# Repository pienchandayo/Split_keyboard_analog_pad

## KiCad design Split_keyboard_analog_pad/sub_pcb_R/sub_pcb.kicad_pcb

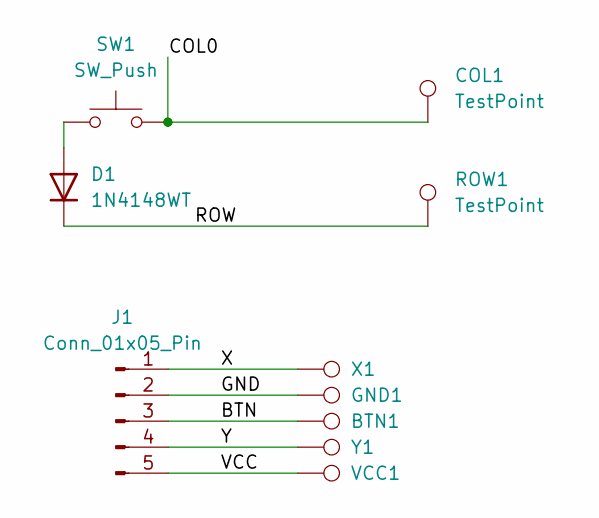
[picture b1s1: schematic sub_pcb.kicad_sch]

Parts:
BTN1: TestPoint; TestPoint_Pad_1.5x1.5mm
COL1: TestPoint; TestPoint_Pad_1.5x1.5mm
D1: 1N4148WT; D_SOD-523
GND1: TestPoint; TestPoint_Pad_1.5x1.5mm
J1: Conn_01x05_Pin; Switch_joy_pad
ROW1: TestPoint; TestPoint_Pad_1.5x1.5mm
SW1: SW_Push; SW_Kailh_Choc_V1V2_1.00u
VCC1: TestPoint; TestPoint_Pad_1.5x1.5mm
X1: TestPoint; TestPoint_Pad_1.5x1.5mm
Y1: TestPoint; TestPoint_Pad_1.5x1.5mm

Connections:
/BTN: BTN1.1, J1.3
/COL0: COL1.1, SW1.2
/GND: GND1.1, J1.2
/ROW: D1.1 (K), ROW1.1
/VCC: J1.5, VCC1.1
/X: J1.1, X1.1
/Y: J1.4, Y1.1
unnamed: D1.2 (A), SW1.1

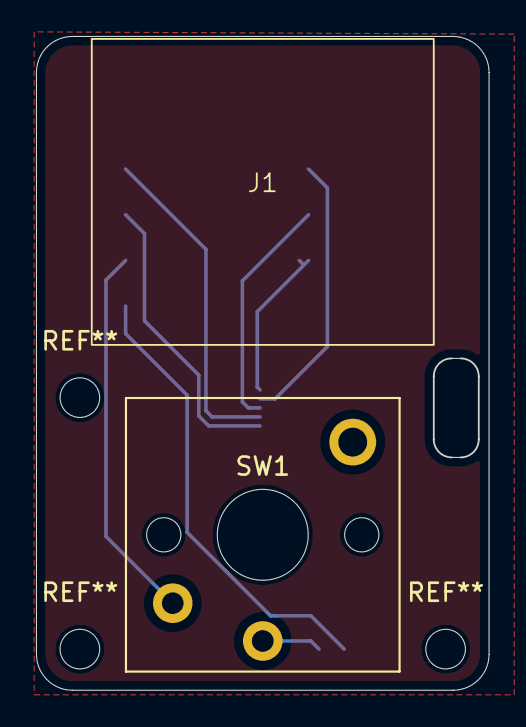
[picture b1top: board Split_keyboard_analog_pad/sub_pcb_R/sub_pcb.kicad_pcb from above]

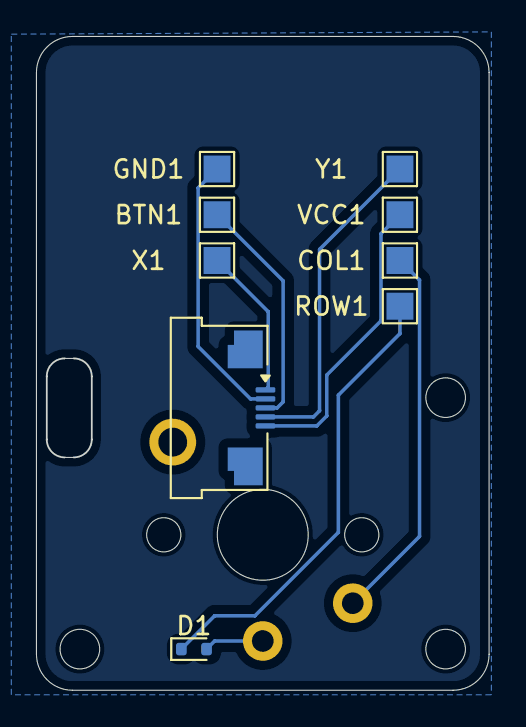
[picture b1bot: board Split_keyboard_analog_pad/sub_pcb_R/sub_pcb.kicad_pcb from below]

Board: 2 copper layers, 25.1 x 36.3 mm, 10 parts (8 on the bottom side), 8 nets.

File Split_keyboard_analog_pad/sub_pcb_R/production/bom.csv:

Designator,Footprint,Quantity,Value,LCSC Part #
"BTN1, COL1, GND1, ROW1, VCC1, X1, Y1",TestPoint_Pad_1.5x1.5mm,7,TestPoint,
D1,D_SOD-523,1,1N4148WT,
J1,Switch_joy_pad,1,Conn_01x05_Pin,
SW1,SW_Kailh_Choc_V1V2_1.00u,1,SW_Push,

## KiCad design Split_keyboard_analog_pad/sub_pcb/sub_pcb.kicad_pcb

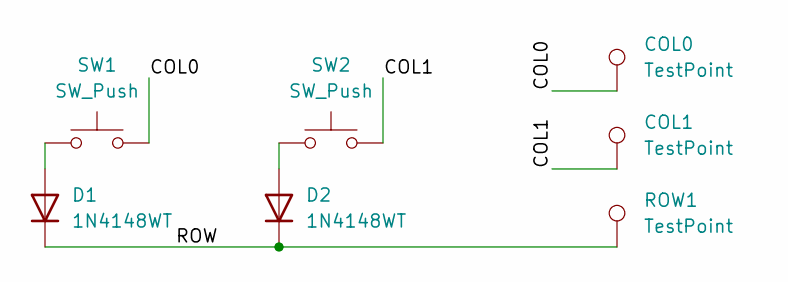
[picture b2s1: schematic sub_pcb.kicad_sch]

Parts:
COL0, COL1: TestPoint; TestPoint_Pad_1.5x1.5mm
D1, D2: 1N4148WT; D_SOD-523
ROW1: TestPoint; TestPoint_Pad_1.5x1.5mm
SW1, SW2: SW_Push; SW_Kailh_Choc_V1V2_1.00u

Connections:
/COL0: COL0.1, SW1.2
/COL1: COL1.1, SW2.2
/ROW: D1.1 (K), D2.1 (K), ROW1.1
unnamed: D1.2 (A), SW1.1
unnamed: D2.2 (A), SW2.1

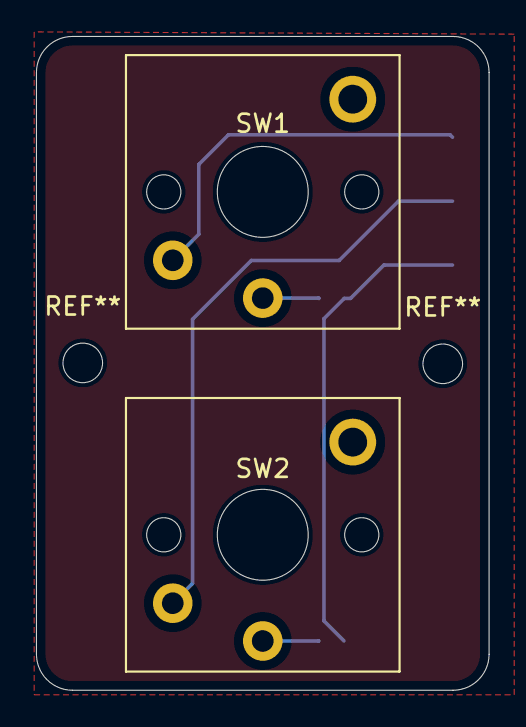
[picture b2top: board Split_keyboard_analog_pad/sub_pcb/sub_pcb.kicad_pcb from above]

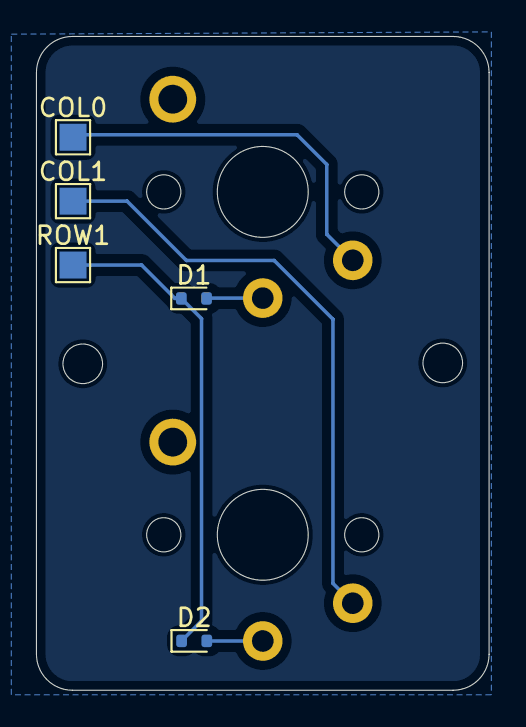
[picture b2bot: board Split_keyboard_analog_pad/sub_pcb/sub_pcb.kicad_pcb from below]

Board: 2 copper layers, 25.1 x 36.3 mm, 7 parts (5 on the bottom side), 5 nets.

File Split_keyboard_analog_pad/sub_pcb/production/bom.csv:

Designator,Footprint,Quantity,Value,LCSC Part #
"COL0, COL1, ROW1",TestPoint_Pad_1.5x1.5mm,3,TestPoint,
"D1, D2",D_SOD-523,2,1N4148WT,
"SW1, SW2",SW_Kailh_Choc_V1V2_1.00u,2,SW_Push,

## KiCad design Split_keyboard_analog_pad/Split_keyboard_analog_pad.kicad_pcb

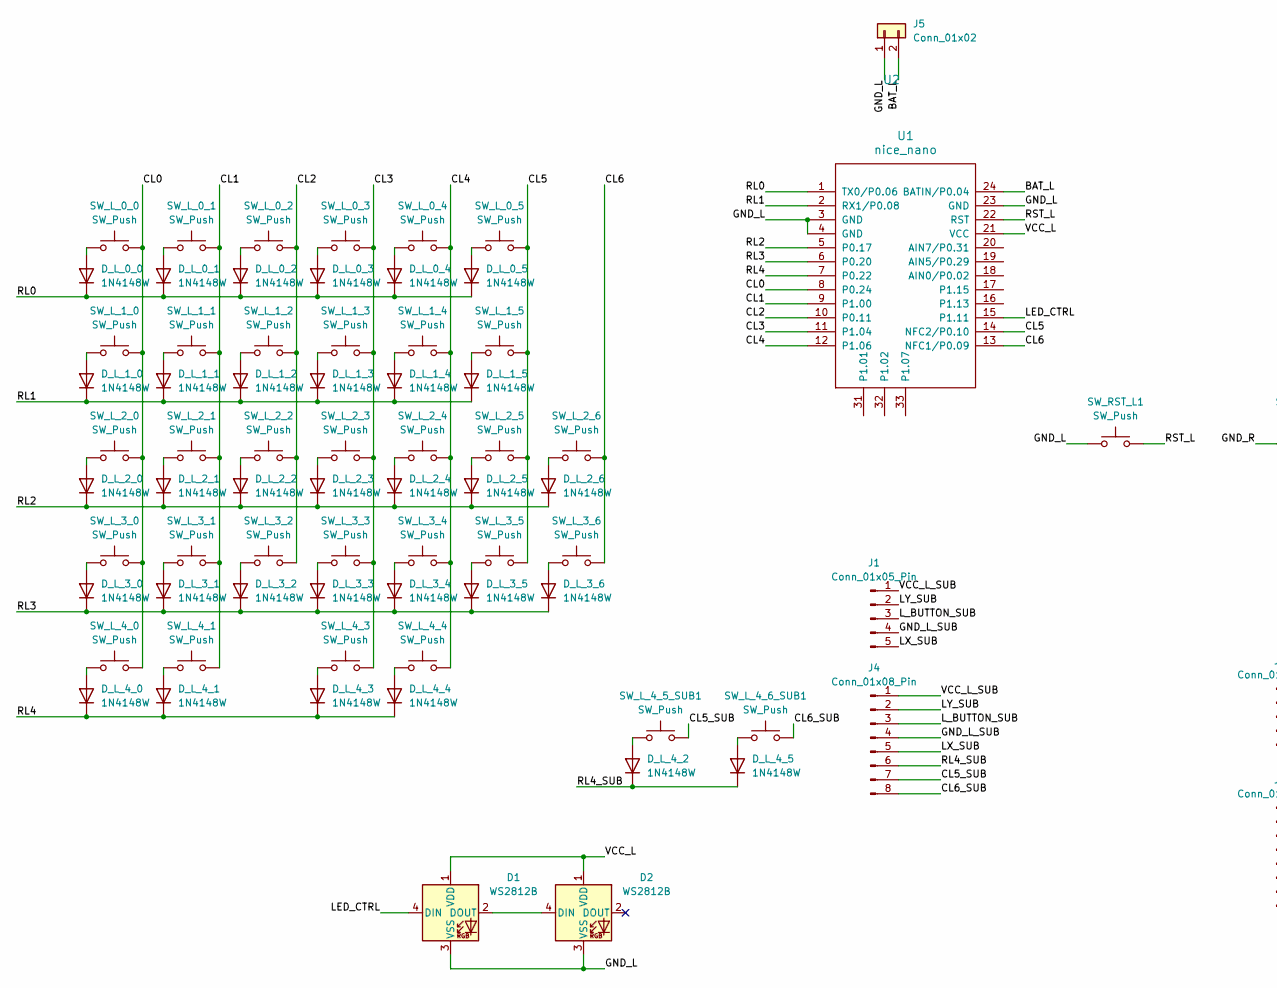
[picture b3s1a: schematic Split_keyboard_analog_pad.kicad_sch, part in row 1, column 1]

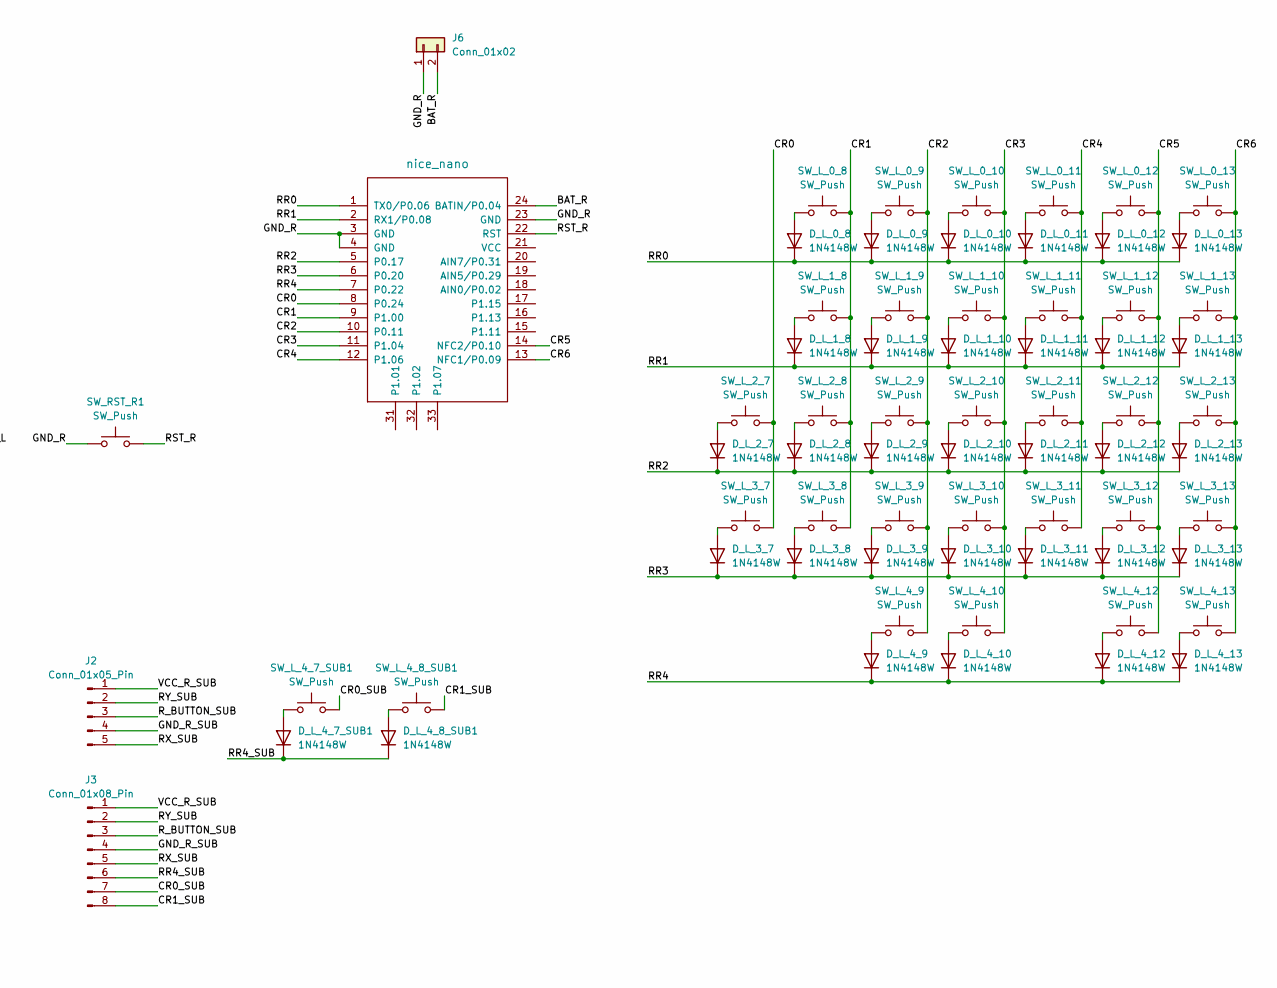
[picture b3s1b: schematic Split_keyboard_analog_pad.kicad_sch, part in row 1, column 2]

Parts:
D1, D2: WS2812B; LED_WS2812B_PLCC4_5.0x5.0mm_P3.2mm
D_L_0_0, D_L_0_1, D_L_0_2, D_L_0_3, D_L_0_4, D_L_0_5, D_L_0_8, D_L_0_9, D_L_0_10, D_L_0_11, D_L_0_12, D_L_0_13, D_L_1_0, D_L_1_1, D_L_1_2, D_L_1_3, D_L_1_4, D_L_1_5, D_L_1_8, D_L_1_9, D_L_1_10, D_L_1_11, D_L_1_12, D_L_1_13, D_L_2_0, D_L_2_1, D_L_2_2, D_L_2_3, D_L_2_4, D_L_2_5, D_L_2_6, D_L_2_7, D_L_2_8, D_L_2_9, D_L_2_10, D_L_2_11, D_L_2_12, D_L_2_13, D_L_3_0, D_L_3_1, D_L_3_2, D_L_3_3, D_L_3_4, D_L_3_5, D_L_3_6, D_L_3_7, D_L_3_8, D_L_3_9, D_L_3_10, D_L_3_11, D_L_3_12, D_L_3_13, D_L_4_0, D_L_4_1, D_L_4_2, D_L_4_3, D_L_4_4, D_L_4_5, D_L_4_7_SUB1, D_L_4_8_SUB1, D_L_4_9, D_L_4_10, D_L_4_12, D_L_4_13: 1N4148W; D_SOD-123
J1, J2: Conn_01x05_Pin; Switch_joy_pad
J3, J4: Conn_01x08_Pin; PinHeader_1x08_P2.54mm_Vertical
J5, J6: Conn_01x02; JST_PH_S2B-PH-SM4-TB_1x02-1MP_P2.00mm_Horizontal
SW_L_0_0, SW_L_0_1, SW_L_0_2, SW_L_0_3, SW_L_0_4, SW_L_0_5, SW_L_0_8, SW_L_0_9, SW_L_0_10, SW_L_0_11, SW_L_0_12, SW_L_0_13, SW_L_1_0, SW_L_1_1, SW_L_1_2, SW_L_1_3, SW_L_1_4, SW_L_1_5, SW_L_1_8, SW_L_1_9, SW_L_1_10, SW_L_1_11, SW_L_1_12, SW_L_1_13, SW_L_2_0, SW_L_2_1, SW_L_2_2, SW_L_2_3, SW_L_2_4, SW_L_2_5, SW_L_2_6, SW_L_2_7, SW_L_2_8, SW_L_2_9, SW_L_2_10, SW_L_2_11, SW_L_2_12, SW_L_2_13, SW_L_3_0, SW_L_3_1, SW_L_3_2, SW_L_3_3, SW_L_3_4, SW_L_3_5, SW_L_3_6, SW_L_3_7, SW_L_3_8, SW_L_3_9, SW_L_3_10, SW_L_3_11, SW_L_3_12, SW_L_3_13, SW_L_4_0, SW_L_4_1, SW_L_4_3, SW_L_4_10, SW_L_4_12, SW_L_4_13: SW_Push; SW_Hotswap_Kailh_MX_1.00u
SW_L_4_4, SW_L_4_9: SW_Push; SW_Hotswap_Kailh_MX_2.00u
SW_L_4_5_SUB1, SW_L_4_6_SUB1, SW_L_4_7_SUB1, SW_L_4_8_SUB1: SW_Push; SW_Kailh_Choc_V2_1.00u
SW_RST_L1: SW_Push; SW_SPST_Omron_B3FS-100xP
SW_RST_R1: SW_Push; SW_SPST_Omron_B3FS-100xP
U1, U2: nice_nano

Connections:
/BAT_L: J5.2, U1.24 (BATIN/P0.04)
/BAT_R: J6.2, U2.24 (BATIN/P0.04)
/CL0: SW_L_0_0.2, SW_L_1_0.2, SW_L_2_0.2, SW_L_3_0.2, SW_L_4_0.2, U1.8 (P0.24)
/CL1: SW_L_0_1.2, SW_L_1_1.2, SW_L_2_1.2, SW_L_3_1.2, SW_L_4_1.2, U1.9 (P1.00)
/CL2: SW_L_0_2.2, SW_L_1_2.2, SW_L_2_2.2, SW_L_3_2.2, U1.10 (P0.11)
/CL3: SW_L_0_3.2, SW_L_1_3.2, SW_L_2_3.2, SW_L_3_3.2, SW_L_4_3.2, U1.11 (P1.04)
/CL4: SW_L_0_4.2, SW_L_1_4.2, SW_L_2_4.2, SW_L_3_4.2, SW_L_4_4.2, U1.12 (P1.06)
/CL5: SW_L_0_5.2, SW_L_1_5.2, SW_L_2_5.2, SW_L_3_5.2, U1.14 (NFC2/P0.10)
/CL5_SUB: J4.7, SW_L_4_5_SUB1.2
/CL6: SW_L_2_6.2, SW_L_3_6.2, U1.13 (NFC1/P0.09)
/CL6_SUB: J4.8, SW_L_4_6_SUB1.2
/CR0: SW_L_2_7.2, SW_L_3_7.2, U2.8 (P0.24)
/CR0_SUB: J3.7, SW_L_4_7_SUB1.2
/CR1: SW_L_0_8.2, SW_L_1_8.2, SW_L_2_8.2, SW_L_3_8.2, U2.9 (P1.00)
/CR1_SUB: J3.8, SW_L_4_8_SUB1.2
/CR2: SW_L_0_9.2, SW_L_1_9.2, SW_L_2_9.2, SW_L_3_9.2, SW_L_4_9.2, U2.10 (P0.11)
/CR3: SW_L_0_10.2, SW_L_1_10.2, SW_L_2_10.2, SW_L_3_10.2, SW_L_4_10.2, U2.11 (P1.04)
/CR4: SW_L_0_11.2, SW_L_1_11.2, SW_L_2_11.2, SW_L_3_11.2, U2.12 (P1.06)
/CR5: SW_L_0_12.2, SW_L_1_12.2, SW_L_2_12.2, SW_L_3_12.2, SW_L_4_12.2, U2.14 (NFC2/P0.10)
/CR6: SW_L_0_13.2, SW_L_1_13.2, SW_L_2_13.2, SW_L_3_13.2, SW_L_4_13.2, U2.13 (NFC1/P0.09)
/GND_L: D1.3 (VSS), D2.3 (VSS), J5.1, SW_RST_L1.1, U1.3 (GND), U1.4 (GND), U1.23 (GND)
/GND_L_SUB: J1.4, J4.4
/GND_R: J6.1, SW_RST_R1.1, U2.3 (GND), U2.4 (GND), U2.23 (GND); also elsewhere on the board
/GND_R_SUB: J2.4, J3.4
/LED_CTRL_L: D1.4 (DIN), U1.15 (P1.11)
/LED_CTRL_R: U2.15 (P1.11); also elsewhere on the board
/LX_SUB: J1.5, J4.5
/LY_SUB: J1.2, J4.2
/L_BUTTON_SUB: J1.3, J4.3
/RL0: D_L_0_0.1 (K), D_L_0_1.1 (K), D_L_0_2.1 (K), D_L_0_3.1 (K), D_L_0_4.1 (K), D_L_0_5.1 (K), U1.1 (TX0/P0.06)
/RL1: D_L_1_0.1 (K), D_L_1_1.1 (K), D_L_1_2.1 (K), D_L_1_3.1 (K), D_L_1_4.1 (K), D_L_1_5.1 (K), U1.2 (RX1/P0.08)
/RL2: D_L_2_0.1 (K), D_L_2_1.1 (K), D_L_2_2.1 (K), D_L_2_3.1 (K), D_L_2_4.1 (K), D_L_2_5.1 (K), D_L_2_6.1 (K), U1.5 (P0.17)
/RL3: D_L_3_0.1 (K), D_L_3_1.1 (K), D_L_3_2.1 (K), D_L_3_3.1 (K), D_L_3_4.1 (K), D_L_3_5.1 (K), D_L_3_6.1 (K), U1.6 (P0.20)
/RL4: D_L_4_0.1 (K), D_L_4_1.1 (K), D_L_4_3.1 (K), D_L_4_4.1 (K), U1.7 (P0.22)
/RL4_SUB: D_L_4_2.1 (K), D_L_4_5.1 (K), J4.6
/RR0: D_L_0_8.1 (K), D_L_0_9.1 (K), D_L_0_10.1 (K), D_L_0_11.1 (K), D_L_0_12.1 (K), D_L_0_13.1 (K), U2.1 (TX0/P0.06)
/RR1: D_L_1_8.1 (K), D_L_1_9.1 (K), D_L_1_10.1 (K), D_L_1_11.1 (K), D_L_1_12.1 (K), D_L_1_13.1 (K), U2.2 (RX1/P0.08)
/RR2: D_L_2_7.1 (K), D_L_2_8.1 (K), D_L_2_9.1 (K), D_L_2_10.1 (K), D_L_2_11.1 (K), D_L_2_12.1 (K), D_L_2_13.1 (K), U2.5 (P0.17)
/RR3: D_L_3_7.1 (K), D_L_3_8.1 (K), D_L_3_9.1 (K), D_L_3_10.1 (K), D_L_3_11.1 (K), D_L_3_12.1 (K), D_L_3_13.1 (K), U2.6 (P0.20)
/RR4: D_L_4_9.1 (K), D_L_4_10.1 (K), D_L_4_12.1 (K), D_L_4_13.1 (K), U2.7 (P0.22)
/RR4_SUB: D_L_4_7_SUB1.1 (K), D_L_4_8_SUB1.1 (K), J3.6
/RST_L: SW_RST_L1.2, U1.22 (RST)
/RST_R: SW_RST_R1.2, U2.22 (RST)
/RX_SUB: J2.5, J3.5
/RY_SUB: J2.2, J3.2
/R_BUTTON_SUB: J2.3, J3.3
/VCC_L: D1.1 (VDD), D2.1 (VDD), U1.21 (VCC)
/VCC_L_SUB: J1.1, J4.1
/VCC_R: U2.21 (VCC); also elsewhere on the board
/VCC_R_SUB: J2.1, J3.1
unnamed: D1.2 (DOUT), D2.4 (DIN)
unnamed: D_L_0_0.2 (A), SW_L_0_0.1
unnamed: D_L_0_1.2 (A), SW_L_0_1.1
unnamed: D_L_0_2.2 (A), SW_L_0_2.1
unnamed: D_L_0_3.2 (A), SW_L_0_3.1
unnamed: D_L_0_4.2 (A), SW_L_0_4.1
unnamed: D_L_0_5.2 (A), SW_L_0_5.1
unnamed: D_L_0_8.2 (A), SW_L_0_8.1
unnamed: D_L_0_9.2 (A), SW_L_0_9.1
unnamed: D_L_0_10.2 (A), SW_L_0_10.1
unnamed: D_L_0_11.2 (A), SW_L_0_11.1
unnamed: D_L_0_12.2 (A), SW_L_0_12.1
unnamed: D_L_0_13.2 (A), SW_L_0_13.1
unnamed: D_L_1_0.2 (A), SW_L_1_0.1
unnamed: D_L_1_1.2 (A), SW_L_1_1.1
unnamed: D_L_1_2.2 (A), SW_L_1_2.1
unnamed: D_L_1_3.2 (A), SW_L_1_3.1
unnamed: D_L_1_4.2 (A), SW_L_1_4.1
unnamed: D_L_1_5.2 (A), SW_L_1_5.1
unnamed: D_L_1_8.2 (A), SW_L_1_8.1
unnamed: D_L_1_9.2 (A), SW_L_1_9.1
unnamed: D_L_1_10.2 (A), SW_L_1_10.1
unnamed: D_L_1_11.2 (A), SW_L_1_11.1
unnamed: D_L_1_12.2 (A), SW_L_1_12.1
unnamed: D_L_1_13.2 (A), SW_L_1_13.1
unnamed: D_L_2_0.2 (A), SW_L_2_0.1
unnamed: D_L_2_1.2 (A), SW_L_2_1.1
unnamed: D_L_2_2.2 (A), SW_L_2_2.1
unnamed: D_L_2_3.2 (A), SW_L_2_3.1
unnamed: D_L_2_4.2 (A), SW_L_2_4.1
unnamed: D_L_2_5.2 (A), SW_L_2_5.1
unnamed: D_L_2_6.2 (A), SW_L_2_6.1
unnamed: D_L_2_7.2 (A), SW_L_2_7.1
unnamed: D_L_2_8.2 (A), SW_L_2_8.1
unnamed: D_L_2_9.2 (A), SW_L_2_9.1
unnamed: D_L_2_10.2 (A), SW_L_2_10.1
unnamed: D_L_2_11.2 (A), SW_L_2_11.1
unnamed: D_L_2_12.2 (A), SW_L_2_12.1
unnamed: D_L_2_13.2 (A), SW_L_2_13.1
unnamed: D_L_3_0.2 (A), SW_L_3_0.1
unnamed: D_L_3_1.2 (A), SW_L_3_1.1
unnamed: D_L_3_2.2 (A), SW_L_3_2.1
unnamed: D_L_3_3.2 (A), SW_L_3_3.1
unnamed: D_L_3_4.2 (A), SW_L_3_4.1
unnamed: D_L_3_5.2 (A), SW_L_3_5.1
unnamed: D_L_3_6.2 (A), SW_L_3_6.1
unnamed: D_L_3_7.2 (A), SW_L_3_7.1
unnamed: D_L_3_8.2 (A), SW_L_3_8.1
unnamed: D_L_3_9.2 (A), SW_L_3_9.1
unnamed: D_L_3_10.2 (A), SW_L_3_10.1
unnamed: D_L_3_11.2 (A), SW_L_3_11.1
unnamed: D_L_3_12.2 (A), SW_L_3_12.1
unnamed: D_L_3_13.2 (A), SW_L_3_13.1
unnamed: D_L_4_0.2 (A), SW_L_4_0.1
unnamed: D_L_4_1.2 (A), SW_L_4_1.1
unnamed: D_L_4_2.2 (A), SW_L_4_5_SUB1.1
unnamed: D_L_4_3.2 (A), SW_L_4_3.1
unnamed: D_L_4_4.2 (A), SW_L_4_4.1
unnamed: D_L_4_5.2 (A), SW_L_4_6_SUB1.1
unnamed: D_L_4_7_SUB1.2 (A), SW_L_4_7_SUB1.1
unnamed: D_L_4_8_SUB1.2 (A), SW_L_4_8_SUB1.1
unnamed: D_L_4_9.2 (A), SW_L_4_9.1
unnamed: D_L_4_10.2 (A), SW_L_4_10.1
unnamed: D_L_4_12.2 (A), SW_L_4_12.1
unnamed: D_L_4_13.2 (A), SW_L_4_13.1

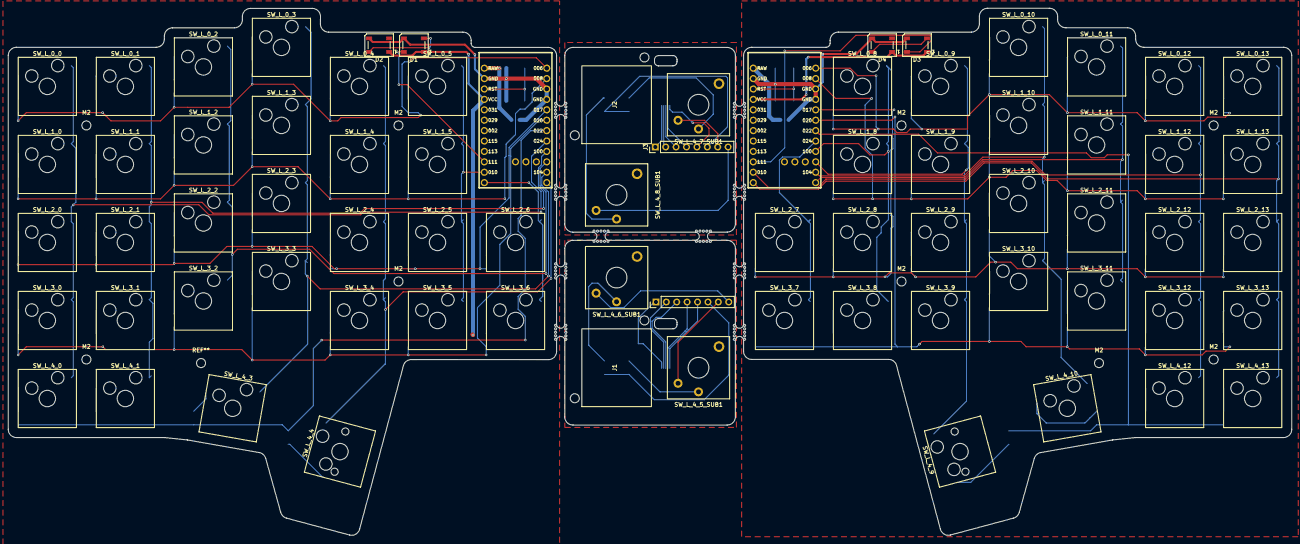
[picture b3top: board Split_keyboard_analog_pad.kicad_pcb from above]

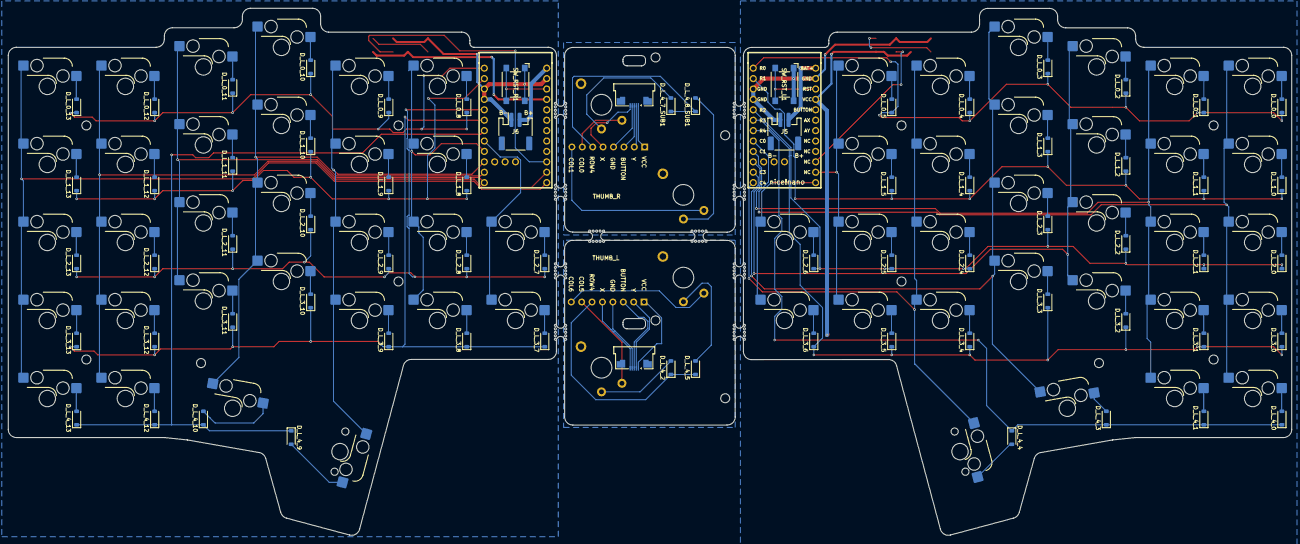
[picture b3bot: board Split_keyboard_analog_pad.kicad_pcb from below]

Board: 2 copper layers, 313.3 x 128.6 mm, 151 parts (70 on the bottom side), 116 nets.

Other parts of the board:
D3, D4: WS2812B; LED_WS2812B_PLCC4_5.0x5.0mm_P3.2mm
M2, M2#2, M2#3, M2#4, M2#5, M2#6, M2#7, M2#8, M2#9: MountingHole_2.2mm_M2

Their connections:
/GND_R: D3.3 (VSS), D4.3 (VSS); also elsewhere on the board
/LED_CTRL_R: D3.4 (DIN); also elsewhere on the board
/VCC_R: D3.1 (VDD), D4.1 (VDD); also elsewhere on the board
unnamed: D3.2 (DOUT), D4.4 (DIN)

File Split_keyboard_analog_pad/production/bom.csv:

Designator,Footprint,Quantity,Value,LCSC Part #
"D1, D2, D3, D4",LED_WS2812B_PLCC4_5.0x5.0mm_P3.2mm,4,WS2812B,
"D_L_0_0, D_L_0_1, D_L_0_10, D_L_0_11, D_L_0_12, D_L_0_13, D_L_0_2, D_L_0_3, D_L_0_4, D_L_0_5, D_L_0_8, D_L_0_9, D_L_1_0, D_L_1_1, D_L_1_10, D_L_1_11, D_L_1_12, D_L_1_13, D_L_1_2, D_L_1_3, D_L_1_4, D_L_1_5, D_L_1_8, D_L_1_9, D_L_2_0, D_L_2_1, D_L_2_10, D_L_2_11, D_L_2_12, D_L_2_13, D_L_2_2, D_L_2_3, D_L_2_4, D_L_2_5, D_L_2_6, D_L_2_7, D_L_2_8, D_L_2_9, D_L_3_0, D_L_3_1, D_L_3_10, D_L_3_11, D_L_3_12, D_L_3_13, D_L_3_2, D_L_3_3, D_L_3_4, D_L_3_5, D_L_3_6, D_L_3_7, D_L_3_8, D_L_3_9, D_L_4_0, D_L_4_1, D_L_4_10, D_L_4_12, D_L_4_13, D_L_4_2, D_L_4_3, D_L_4_4, D_L_4_5, D_L_4_7_SUB1, D_L_4_8_SUB1, D_L_4_9",D_SOD-123,64,1N4148W,
"J1, J2",Switch_joy_pad,2,Conn_01x05_Pin,
"J3, J4",PinHeader_1x08_P2.54mm_Vertical,2,Conn_01x08_Pin,
"J5, J6",JST_PH_S2B-PH-SM4-TB_1x02-1MP_P2.00mm_Horizontal,2,Conn_01x02,
"SW_L_0_0, SW_L_0_1, SW_L_0_10, SW_L_0_11, SW_L_0_12, SW_L_0_13, SW_L_0_2, SW_L_0_3, SW_L_0_4, SW_L_0_5, SW_L_0_8, SW_L_0_9, SW_L_1_0, SW_L_1_1, SW_L_1_10, SW_L_1_11, SW_L_1_12, SW_L_1_13, SW_L_1_2, SW_L_1_3, SW_L_1_4, SW_L_1_5, SW_L_1_8, SW_L_1_9, SW_L_2_0, SW_L_2_1, SW_L_2_10, SW_L_2_11, SW_L_2_12, SW_L_2_13, SW_L_2_2, SW_L_2_3, SW_L_2_4, SW_L_2_5, SW_L_2_6, SW_L_2_7, SW_L_2_8, SW_L_2_9, SW_L_3_0, SW_L_3_1, SW_L_3_10, SW_L_3_11, SW_L_3_12, SW_L_3_13, SW_L_3_2, SW_L_3_3, SW_L_3_4, SW_L_3_5, SW_L_3_6, SW_L_3_7, SW_L_3_8, SW_L_3_9, SW_L_4_0, SW_L_4_1, SW_L_4_10, SW_L_4_12, SW_L_4_13, SW_L_4_3",SW_Hotswap_Kailh_MX_1.00u,58,SW_Push,
"SW_L_4_4, SW_L_4_9",SW_Hotswap_Kailh_MX_2.00u,2,SW_Push,
"SW_L_4_5_SUB1, SW_L_4_6_SUB1, SW_L_4_7_SUB1, SW_L_4_8_SUB1",SW_Kailh_Choc_V2_1.00u,4,SW_Push,
"SW_RST_L1, SW_RST_R1",SW_SPST_Omron_B3FS-100xP,2,SW_Push,
"U1, U2",nice_nano,2,nice_nano,

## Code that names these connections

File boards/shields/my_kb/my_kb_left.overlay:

#include "my_kb.dtsi"

/ {
    chosen {
        zmk,kscan = &kscan0;
    };

    kscan0: kscan {
        compatible = "zmk,kscan-gpio-matrix";
        diode-direction = "col2row";

        col-gpios
            = <&gpio0 24 GPIO_ACTIVE_HIGH> // COL0
            , <&gpio0 11 GPIO_ACTIVE_HIGH> // COL2
            , <&gpio1  0 GPIO_ACTIVE_HIGH> // COL1
            , <&gpio1  4 GPIO_ACTIVE_HIGH> // COL3
            , <&gpio1  6 GPIO_ACTIVE_HIGH> // COL4
            , <&gpio0 10 GPIO_ACTIVE_HIGH> // COL5
            , <&gpio0  9 GPIO_ACTIVE_HIGH> // COL6
            ;

        row-gpios
            = <&gpio0  6 (GPIO_ACTIVE_HIGH | GPIO_PULL_DOWN)> // ROW0
            , <&gpio0  8 (GPIO_ACTIVE_HIGH | GPIO_PULL_DOWN)> // ROW1
            , <&gpio0 17 (GPIO_ACTIVE_HIGH | GPIO_PULL_DOWN)> // ROW2
            , <&gpio0 20 (GPIO_ACTIVE_HIGH | GPIO_PULL_DOWN)> // ROW3
            , <&gpio0 22 (GPIO_ACTIVE_HIGH | GPIO_PULL_DOWN)> // ROW4
            ;
    };
};

&default_transform { // Offset of 3 because the left side has 3 columns
        col-offset = <7>;
    };

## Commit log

2026-03-01 Add my_kb split wireless configuration
2026-03-01 Add my_kb split wireless configuration fixed
2026-03-01 Add my_kb split wireless configuration fixed1
2026-03-01 Add my_kb split wireless configuration fixed2
2026-03-01 Add my_kb split wireless configuration fixed3
2026-03-22 Update kscan according to the latest layout
2026-03-22 update_kscan
2026-03-22 Add analog pad button to kscan
2026-03-24 remove LED definition
2026-03-24 Add layer1 definition
2026-03-24 Add physical layout and enable ZMK studio
2026-03-26 Update layout
2026-03-26 Update key map
2026-03-26 add physical layout
2026-03-26 REMOVE ZMK studio
2026-03-26 add double click macro
2026-04-02 Add BT profile select hold tap
2026-04-05 Update BT behavior
2026-04-19 UPDATE DEAD ZONE TO FIX dRIFT
2026-04-19 debug mouse function
2026-04-19 split enable
2026-04-19 Update role
2026-04-19 Update BLE power
2026-06-14 update keymap
2026-06-14 change keymap, update pointer speed
2026-06-14 fixed
2026-06-14 fix kscan
2026-06-14 fix kscan
2026-06-16 update kscan
2026-06-17 kscan
2026-06-18 update ksncan
2026-06-18 simple kscan
